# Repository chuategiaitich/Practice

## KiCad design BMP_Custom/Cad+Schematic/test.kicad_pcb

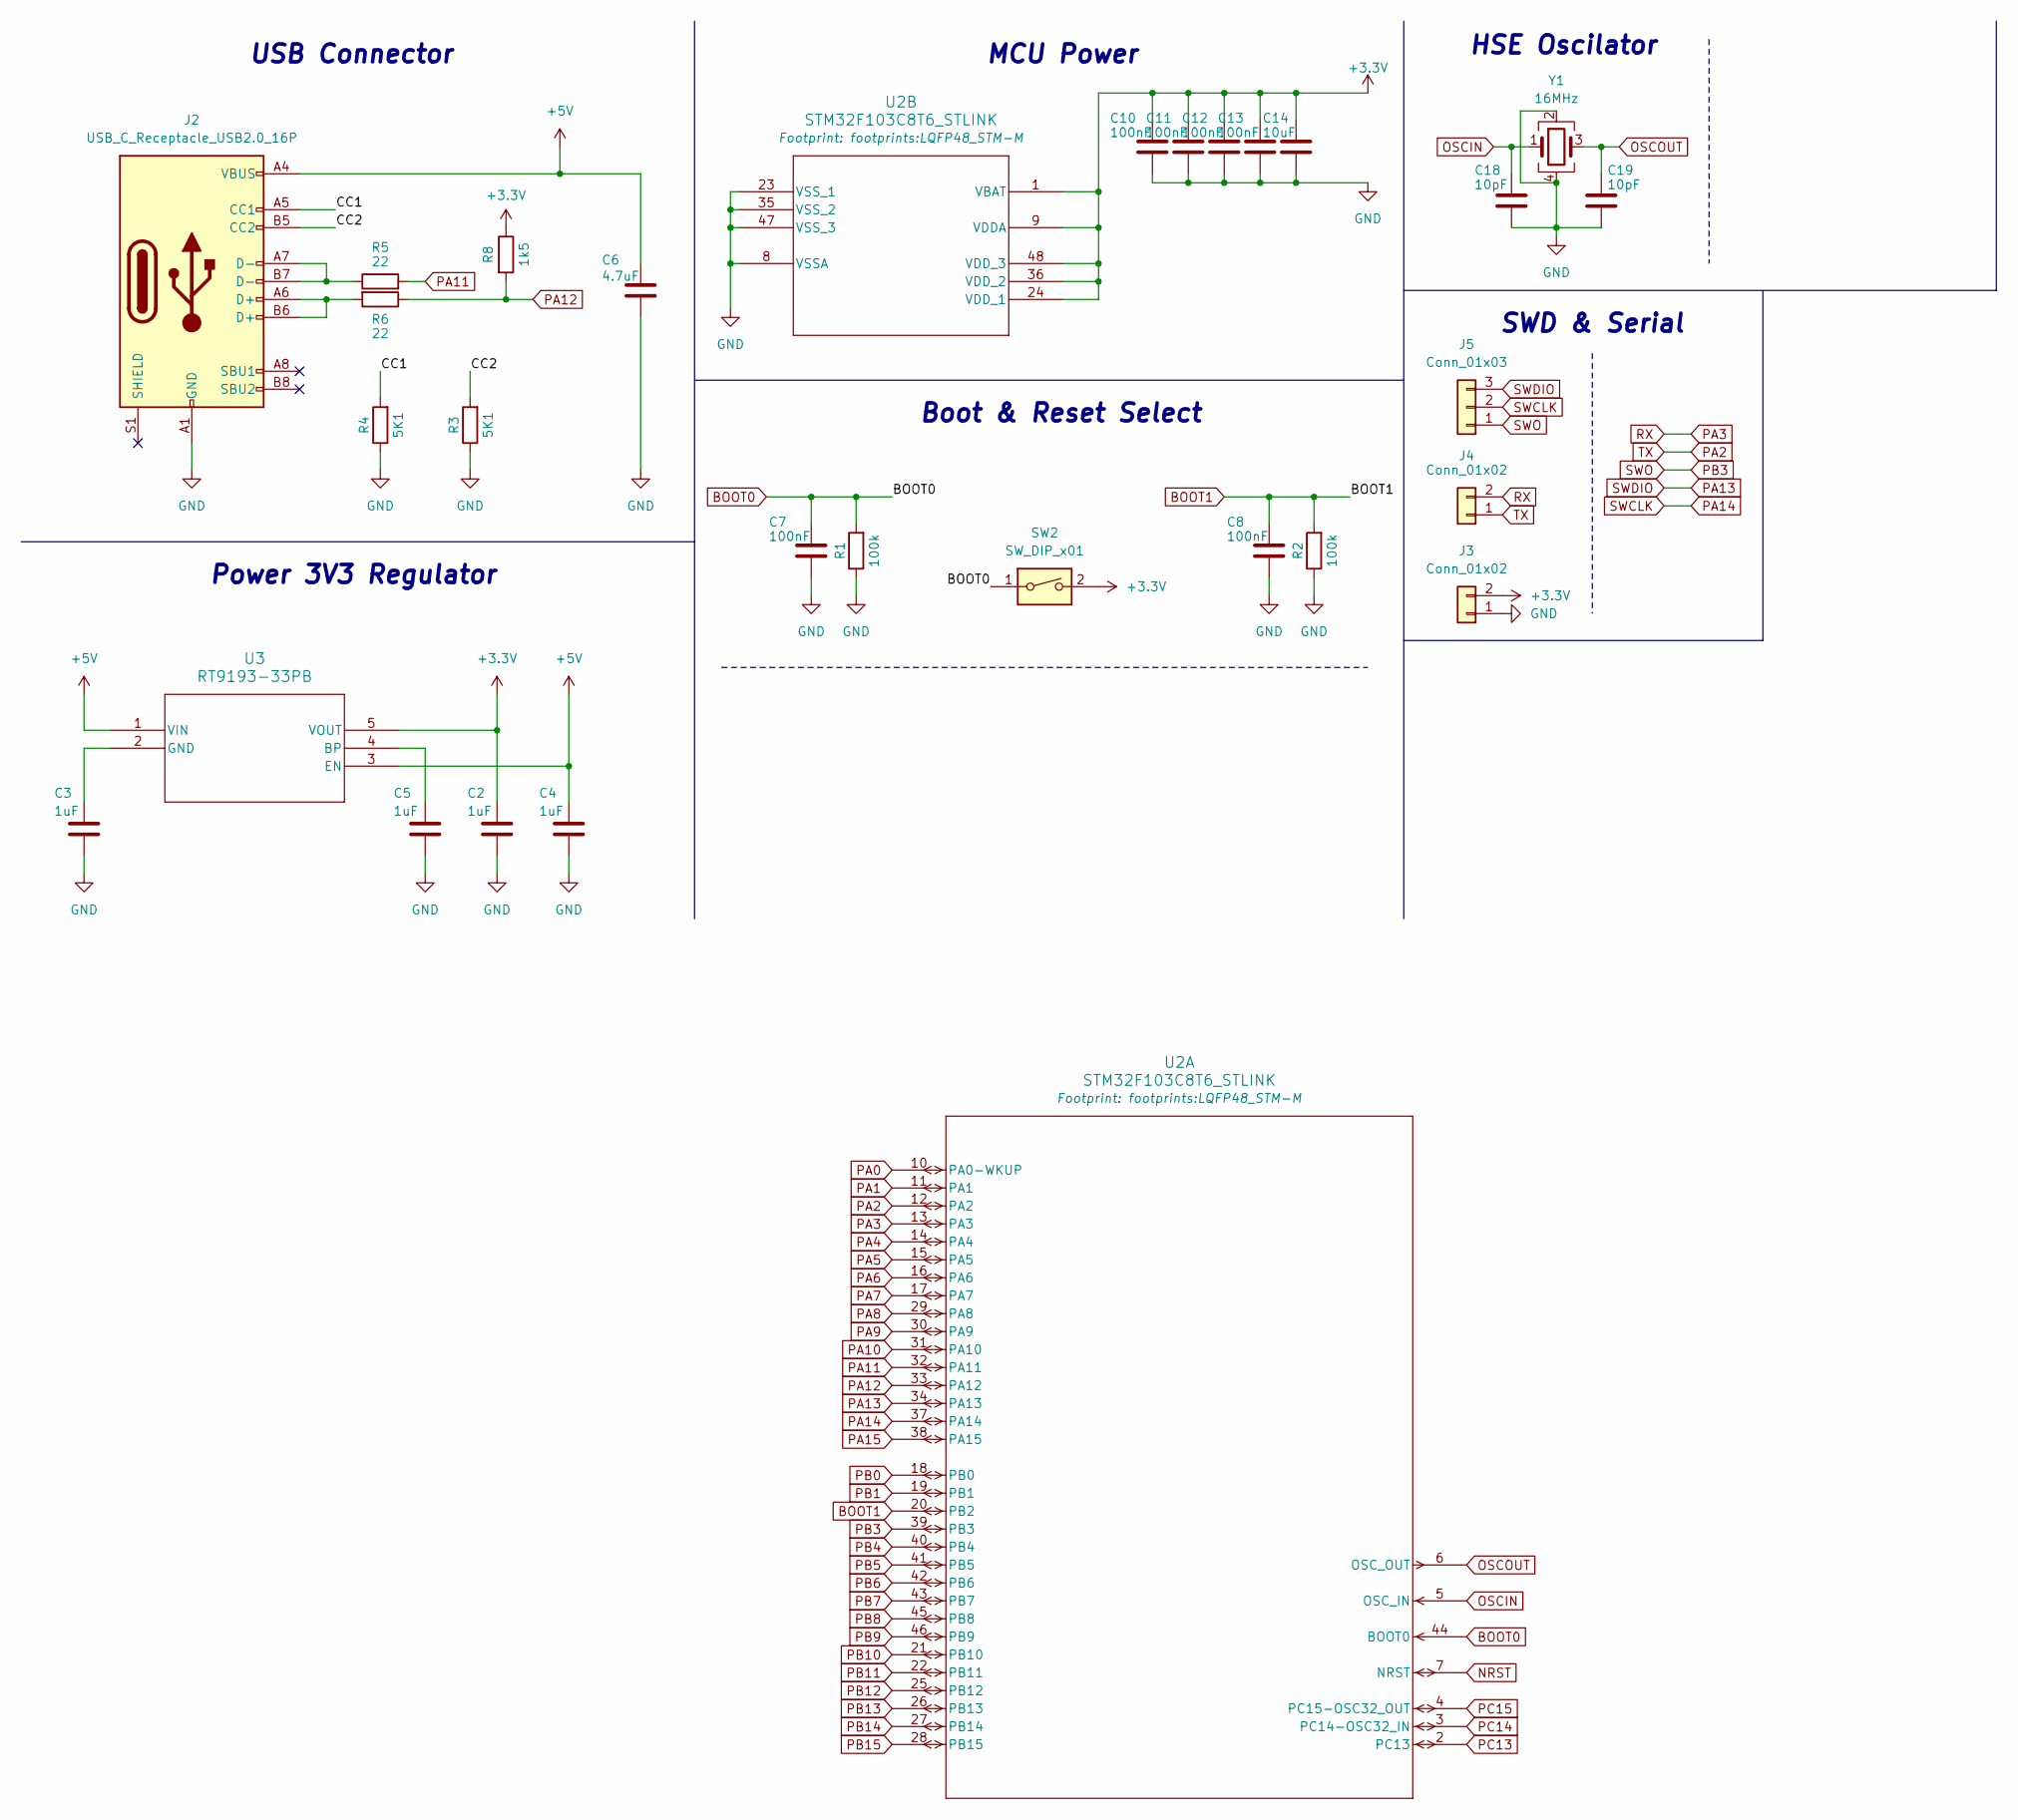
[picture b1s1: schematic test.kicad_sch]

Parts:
C2, C3, C4, C5: 1uF; C_0201_0603Metric
C6: 4.7uF; C_0201_0603Metric
C7, C8, C10, C11, C12, C13: 100nF; C_0201_0603Metric
C14: 10uF; C_0201_0603Metric
C18, C19: 10pF; C_0201_0603Metric
J2: USB_C_Receptacle_USB2.0_16P; USB_C_Receptacle_GCT_USB4105-xx-A_16P_TopMnt_Horizontal
J3, J4: Conn_01x02; PinHeader_1x02_P2.54mm_Vertical
J5: Conn_01x03; PinHeader_1x03_P2.54mm_Vertical
R1, R2: 100k; R_0201_0603Metric
R3, R4: 5K1; R_0201_0603Metric
R5, R6: 22; R_0201_0603Metric
R8: 1k5; R_0201_0603Metric
SW2: SW_DIP_x01; SW_DIP_SPSTx01_Slide_9.78x4.72mm_W7.62mm_P2.54mm
U2: STM32F103C8T6_STLINK; LQFP48_STM-M
U3: RT9193-33PB; SC-70-5_RIT
Y1: 16MHz; Crystal_SMD_5032-4Pin_5.0x3.2mm

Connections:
+3.3V: C2.1, C10.1, C11.1, C12.1, C13.1, C14.1, J3.2, R8.1, SW2.2, U2.1 (VBAT), U2.9 (VDDA), U2.24 (VDD_1), U2.36 (VDD_2), U2.48 (VDD_3), U3.5 (VOUT)
+5V: C4.1, C6.1, J2.A4 (VBUS), J2.A9 (VBUS), J2.B4 (VBUS), J2.B9 (VBUS), U3.1 (VIN), U3.3 (EN)
/CC1: J2.A5 (CC1), R4.2
/CC2: J2.B5 (CC2), R3.2
BOOT0: C7.1, R1.2, SW2.1, U2.44 (BOOT0)
BOOT1: C8.1, R2.2, U2.20 (PB2)
GND: C2.2, C3.2, C4.2, C5.2, C6.2, C7.2, C8.2, C10.2, C11.2, C12.2, C13.2, C14.2, C18.2, C19.2, J2.A1 (GND), J2.A12 (GND), J2.B1 (GND), J2.B12 (GND), J3.1, R1.1, R2.1, R3.1, R4.1, U2.8 (VSSA), U2.23 (VSS_1), U2.35 (VSS_2), U2.47 (VSS_3), Y1.2, Y1.4
NRST: U2.7 (NRST)
unnamed: J2.A6 (D+), J2.B6 (D+), R6.2
unnamed: J2.A7 (D-), J2.B7 (D-), R5.1
unnamed: C5.1, U3.4 (BP)
unnamed: C3.1, U3.2 (GND)
OSCIN: C18.1, U2.5 (OSC_IN), Y1.1
OSCOUT: C19.1, U2.6 (OSC_OUT), Y1.3
PA0: U2.10 (PA0-WKUP)
PA1: U2.11 (PA1)
PA2: J4.1, U2.12 (PA2)
PA3: J4.2, U2.13 (PA3)
PA4: U2.14 (PA4)
PA5: U2.15 (PA5)
PA6: U2.16 (PA6)
PA7: U2.17 (PA7)
PA8: U2.29 (PA8)
PA9: U2.30 (PA9)
PA10: U2.31 (PA10)
PA11: R5.2, U2.32 (PA11)
PA12: R6.1, R8.2, U2.33 (PA12)
PA13: J5.3, U2.34 (PA13)
PA14: J5.2, U2.37 (PA14)
PA15: U2.38 (PA15)
PB0: U2.18 (PB0)
PB1: U2.19 (PB1)
PB3: J5.1, U2.39 (PB3)
PB4: U2.40 (PB4)
PB5: U2.41 (PB5)
PB6: U2.42 (PB6)
PB7: U2.43 (PB7)
PB8: U2.45 (PB8)
PB9: U2.46 (PB9)
PB10: U2.21 (PB10)
PB11: U2.22 (PB11)
PB12: U2.25 (PB12)
PB13: U2.26 (PB13)
PB14: U2.27 (PB14)
PB15: U2.28 (PB15)
PC13: U2.2 (PC13)
PC14: U2.3 (PC14-OSC32_IN)
PC15: U2.4 (PC15-OSC32_OUT)

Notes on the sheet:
HSE Oscilator
SWD & Serial
Power 3V3 Regulator
MCU Power
Boot & Reset Select
USB Connector

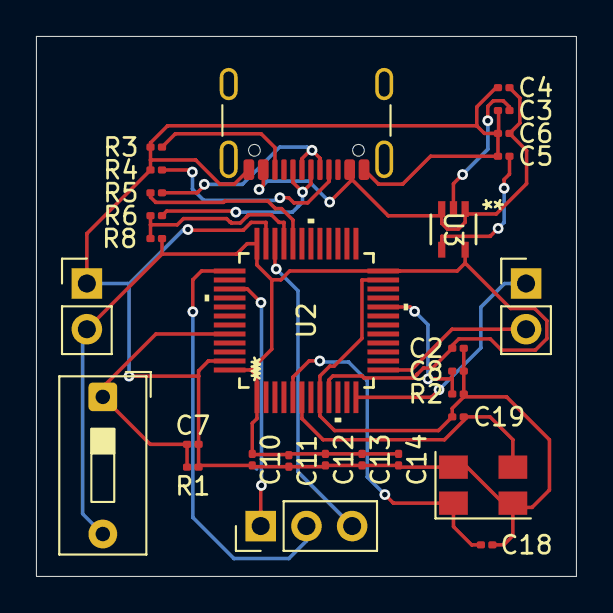
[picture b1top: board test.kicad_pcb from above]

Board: 2 copper layers, 30.0 x 30.0 mm, 29 parts (0 on the bottom side), 20 nets.

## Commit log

2025-05-17 add sipmlefoc+rtos with bluepill
2025-05-17 add plotting GUI
2025-05-17 add sudoku solving
2025-05-26 add odrv
2025-06-21 stlink_custom schematic
2025-07-22 add PID_Tuner
2025-07-22 Repush
